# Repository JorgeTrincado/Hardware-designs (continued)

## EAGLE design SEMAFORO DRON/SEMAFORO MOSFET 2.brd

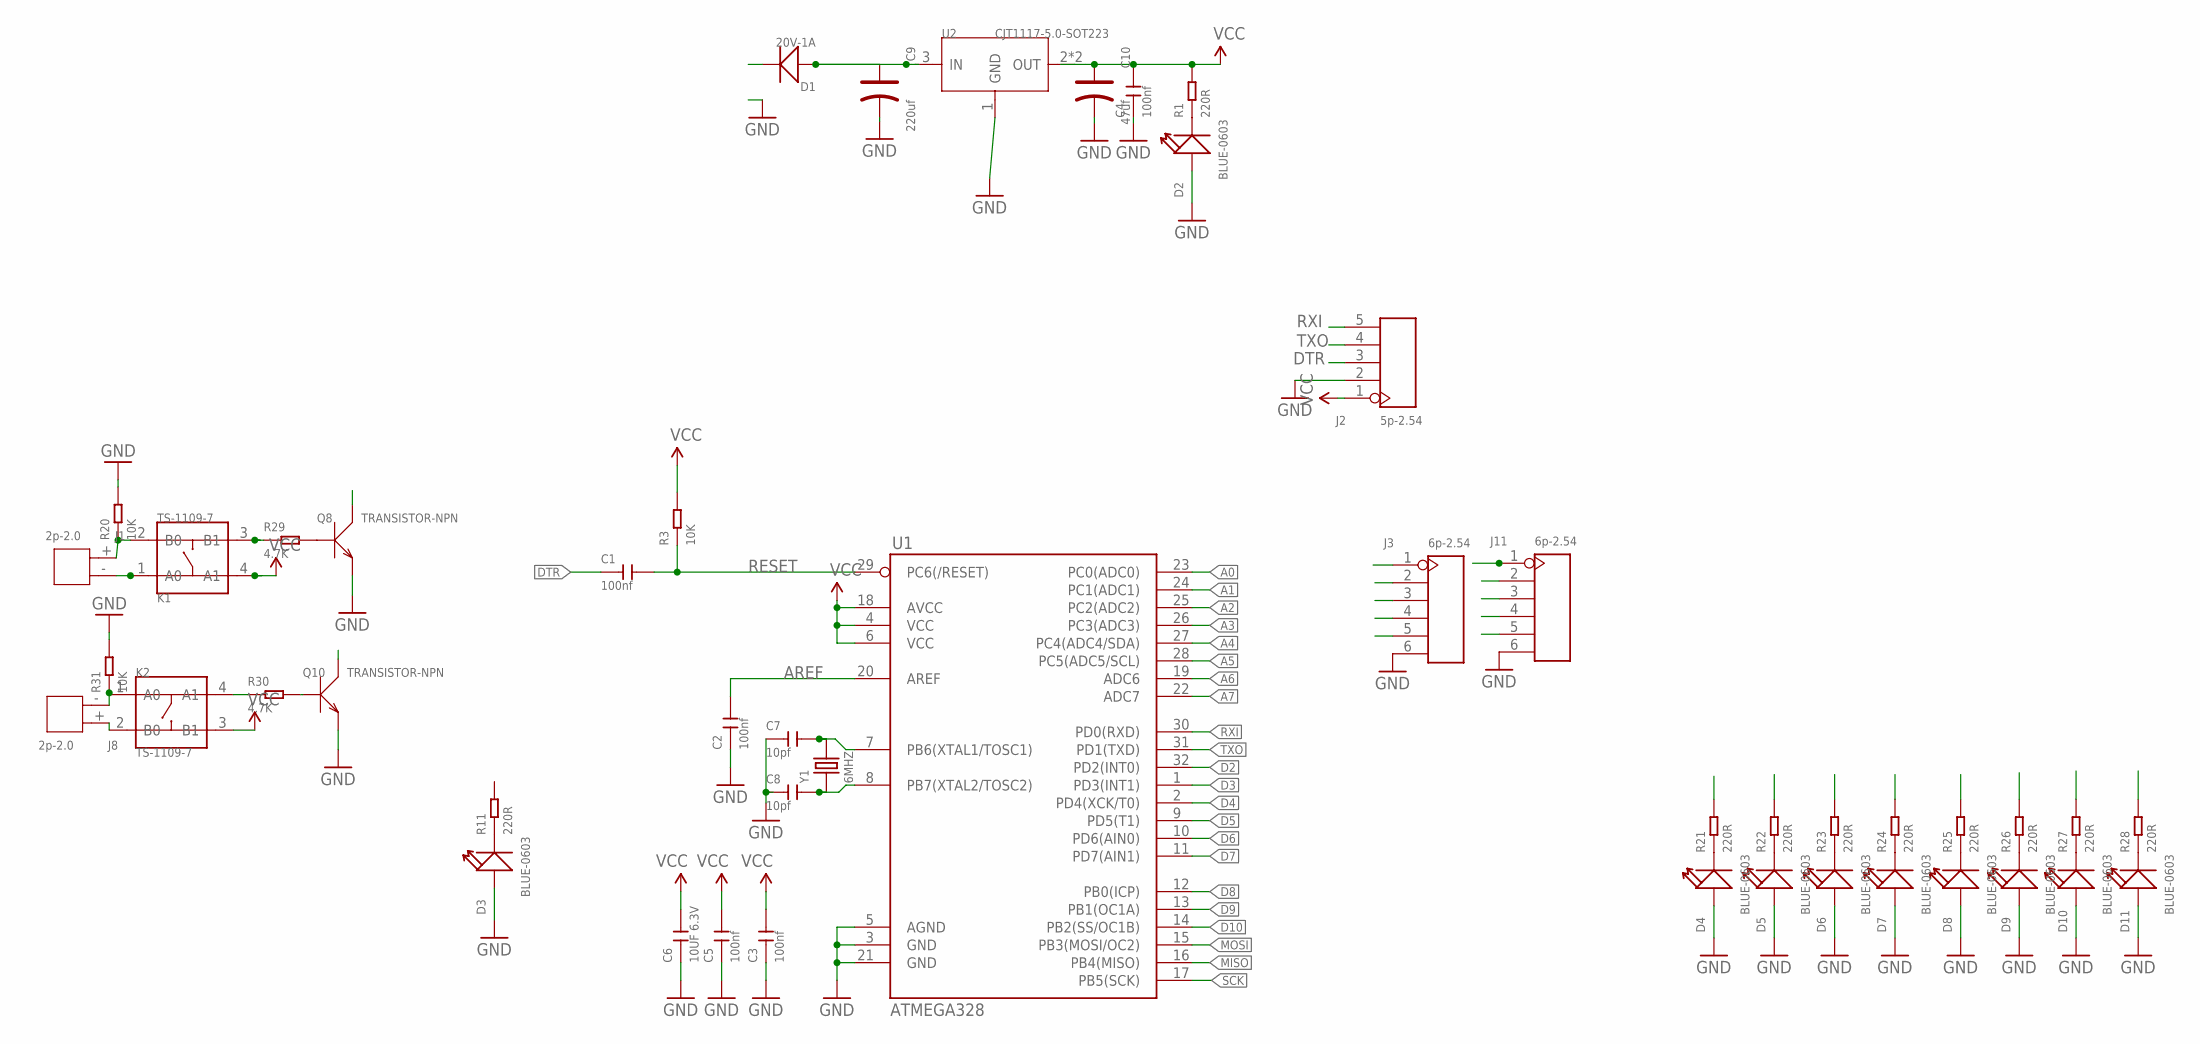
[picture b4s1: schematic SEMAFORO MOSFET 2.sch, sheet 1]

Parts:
C1, C2, C3, C4, C5: 100nf; C0603
C6: 10UF 6.3V; C0603
C7, C8: 10pf; C0603
C9: 220uf; PC-D5.3MM
C10: 47uf; PC-D5.3MM
D1: 20V-1A; SOD-123
D2, D3, D4, D5, D6, D7, D8, D9, D10, D11: BLUE-0603; LED-0603
J1, J8: 2p-2.0; H2-2.0-6X4.5MM
J2: 5p-2.54; H5-2.54
J3, J11: 6p-2.54; H6-2.54
K1, K2: TS-1109-7; SW4-6.2X6.2X5.0MM
Q8, Q10: TRANSISTOR-NPN; SOT-23
R1, R11, R21, R22, R23, R24, R25, R26, R27, R28: 220R; R0603
R3, R20, R31: 10K; R0603
R29, R30: 4.7K; R0603
U1: ATMEGA328; TQFP32-08
U2: CJT1117-5.0-SOT223; SOT-223
Y1: 6MHZ; HC49US

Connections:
3.3V: K1.4 (A1), K2.3 (B1)
A0: J11.3, U1.23 (PC0(ADC0))
A1: J11.2, U1.24 (PC1(ADC1))
A2: J3.5, U1.25 (PC2(ADC2))
A3: J3.4, U1.26 (PC3(ADC3))
A4: J3.3, U1.27 (PC4(ADC4/SDA))
A5: J3.2, U1.28 (PC5(ADC5/SCL))
A6: J11.5, U1.19 (ADC6)
A7: J11.4, U1.22 (ADC7)
AREF: C2.2, U1.20 (AREF)
D2: Q8.3 (C), U1.32 (PD2(INT0))
D3: U1.1 (PD3(INT1))
D4: U1.2 (PD4(XCK/T0))
D5: R21.2, U1.9 (PD5(T1)); also elsewhere on the board
D6: R22.2, U1.10 (PD6(AIN0)); also elsewhere on the board
D7: R23.2, U1.11 (PD7(AIN1)); also elsewhere on the board
D8: R24.2, U1.12 (PB0(ICP)); also elsewhere on the board
D9: R25.2, U1.13 (PB1(OC1A)); also elsewhere on the board
D10: R28.2, U1.14 (PB2(SS/OC1B)); also elsewhere on the board
D22: J1.+, K1.2 (B0), R20.1
DTR: C1.1, J2.3
GND: C2.1, C3.1, C4.1, C5.1, C6.1, C7.1, C8.1, C9.-, C10.-, D2.+, D3.+, D4.+, D5.+, D6.+, D7.+, D8.+, D9.+, D10.+, D11.+, J2.2, J3.6, J11.6, Q8.2 (E), Q10.2 (E), R20.2, R31.2, U1.3 (GND), U1.5 (AGND), U1.21 (GND), U2.1 (GND); also elsewhere on the board
MISO: R26.2, U1.16 (PB4(MISO)); also elsewhere on the board
MOSI: R27.2, U1.15 (PB3(MOSI/OC2)); also elsewhere on the board
unnamed: C8.2, U1.8 (PB7(XTAL2/TOSC2)), Y1.1
unnamed: C7.2, U1.7 (PB6(XTAL1/TOSC1)), Y1.2
unnamed: D2.-, R1.1
unnamed: D4.-, R21.1
unnamed: C9.+, D1.+, U2.3 (IN)
unnamed: D3.-, R11.1
unnamed: J8.-, K2.1 (A0), R31.1
unnamed: J8.+, K2.2 (B0)
unnamed: D5.-, R22.1
unnamed: D6.-, R23.1
unnamed: D7.-, R24.1
unnamed: D8.-, R25.1
unnamed: D9.-, R26.1
unnamed: D10.-, R27.1
unnamed: D11.-, R28.1
unnamed: K2.4 (A1), R30.1
unnamed: K1.3 (B1), R29.1
unnamed: Q10.1 (B), R30.2
unnamed: Q8.1 (B), R29.2
RESET: C1.2, Q10.3 (C), R3.1, U1.29 (PC6(/RESET))
RXI: J2.5, U1.30 (PD0(RXD))
SCK: U1.17 (PB5(SCK))
TXO: J2.4, U1.31 (PD1(TXD))
VCC: C3.2, C4.2, C5.2, C6.2, C10.+, J1.-, J2.1, J3.1, J11.1, K1.1 (A0), R1.2, R3.2, U1.4 (VCC), U1.6 (VCC), U1.18 (AVCC), U2.2 (OUT), U2.TER (OUT)

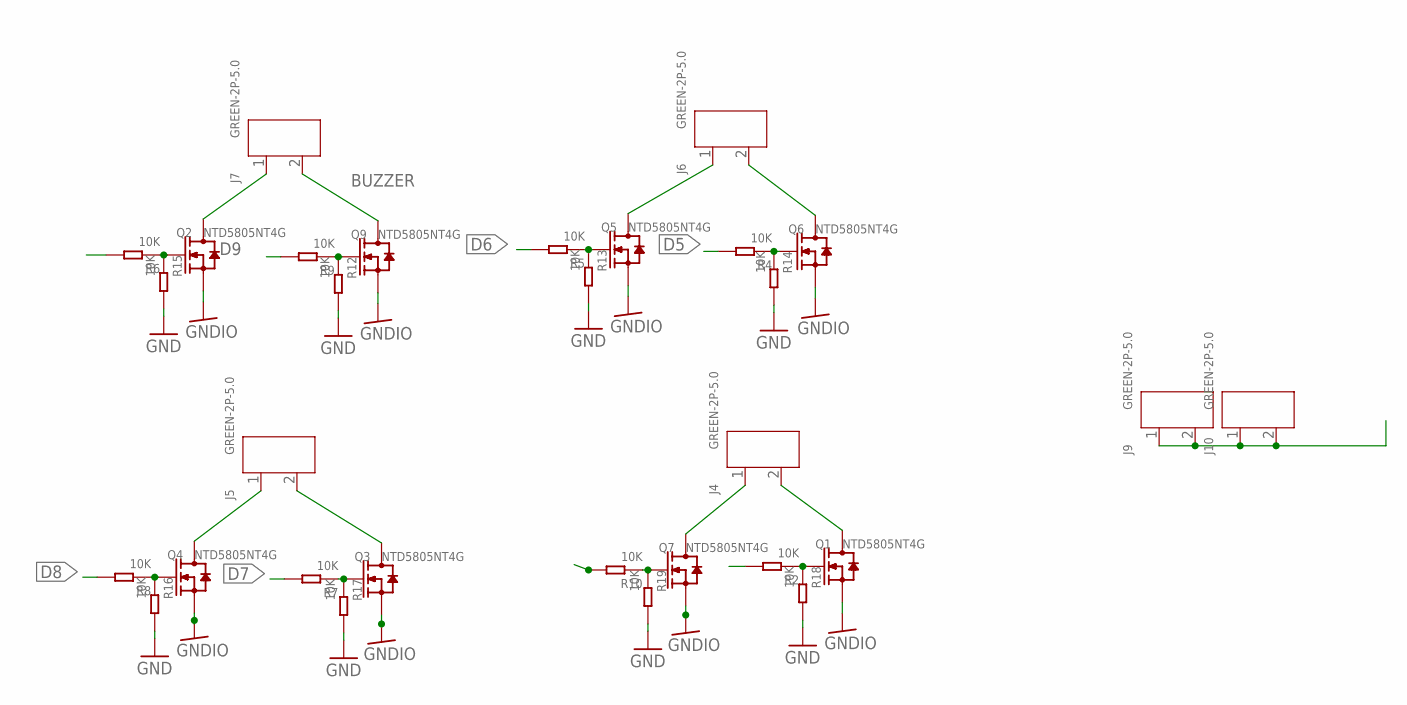
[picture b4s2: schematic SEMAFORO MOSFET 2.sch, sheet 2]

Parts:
J4, J5, J6, J7, J9, J10: GREEN-2P-5.0; H2-5.0-10.5X8.0MM
Q1, Q2, Q3, Q4, Q5, Q6, Q7, Q9: NTD5805NT4G; DPAK
R2, R4, R5, R6, R7, R8, R9, R10, R12, R13, R14, R15, R16, R17, R18, R19: 10K; R0603

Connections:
BUZZER: J7.2, Q9.3 (D)
D5: R4.2; also elsewhere on the board
D6: R5.2; also elsewhere on the board
D7: R7.2; also elsewhere on the board
D8: R8.2; also elsewhere on the board
D9: R9.2; also elsewhere on the board
D10: R6.2; also elsewhere on the board
GND: R12.2, R13.2, R14.2, R15.2, R16.2, R17.2, R18.2, R19.2; also elsewhere on the board
GNDIO: Q1.2 (S), Q2.2 (S), Q3.2 (S), Q4.2 (S), Q5.2 (S), Q6.2 (S), Q7.2 (S), Q9.2 (S)
MISO: R10.2; also elsewhere on the board
MOSI: R2.2; also elsewhere on the board
unnamed: J9.1, J9.2, J10.1, J10.2
unnamed: J4.1, Q7.3 (D)
unnamed: Q1.1 (G), R2.1, R18.1
unnamed: Q6.1 (G), R4.1, R14.1
unnamed: Q9.1 (G), R9.1, R12.1
unnamed: Q7.1 (G), R10.1, R19.1
unnamed: Q5.1 (G), R5.1, R13.1
unnamed: Q2.1 (G), R6.1, R15.1
unnamed: Q3.1 (G), R7.1, R17.1
unnamed: Q4.1 (G), R8.1, R16.1
R1: J5.1, Q4.3 (D)
R2: J5.2, Q3.3 (D)
R3: J6.1, Q5.3 (D)
V1: J6.2, Q6.3 (D)
V2: J4.2, Q1.3 (D)
V3: J7.1, Q2.3 (D)

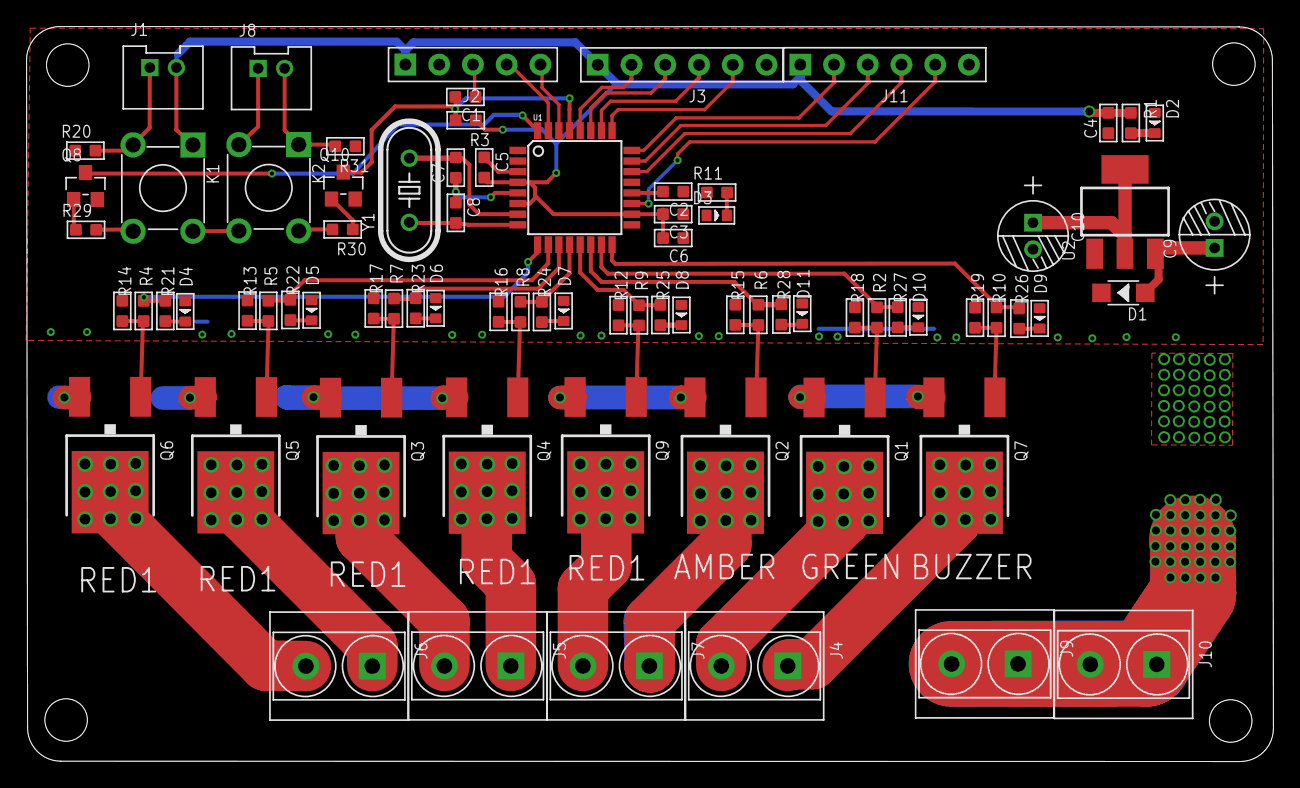
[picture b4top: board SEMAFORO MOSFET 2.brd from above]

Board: 2 copper layers, 93.9 x 55.3 mm, 78 parts (0 on the bottom side), 63 nets.

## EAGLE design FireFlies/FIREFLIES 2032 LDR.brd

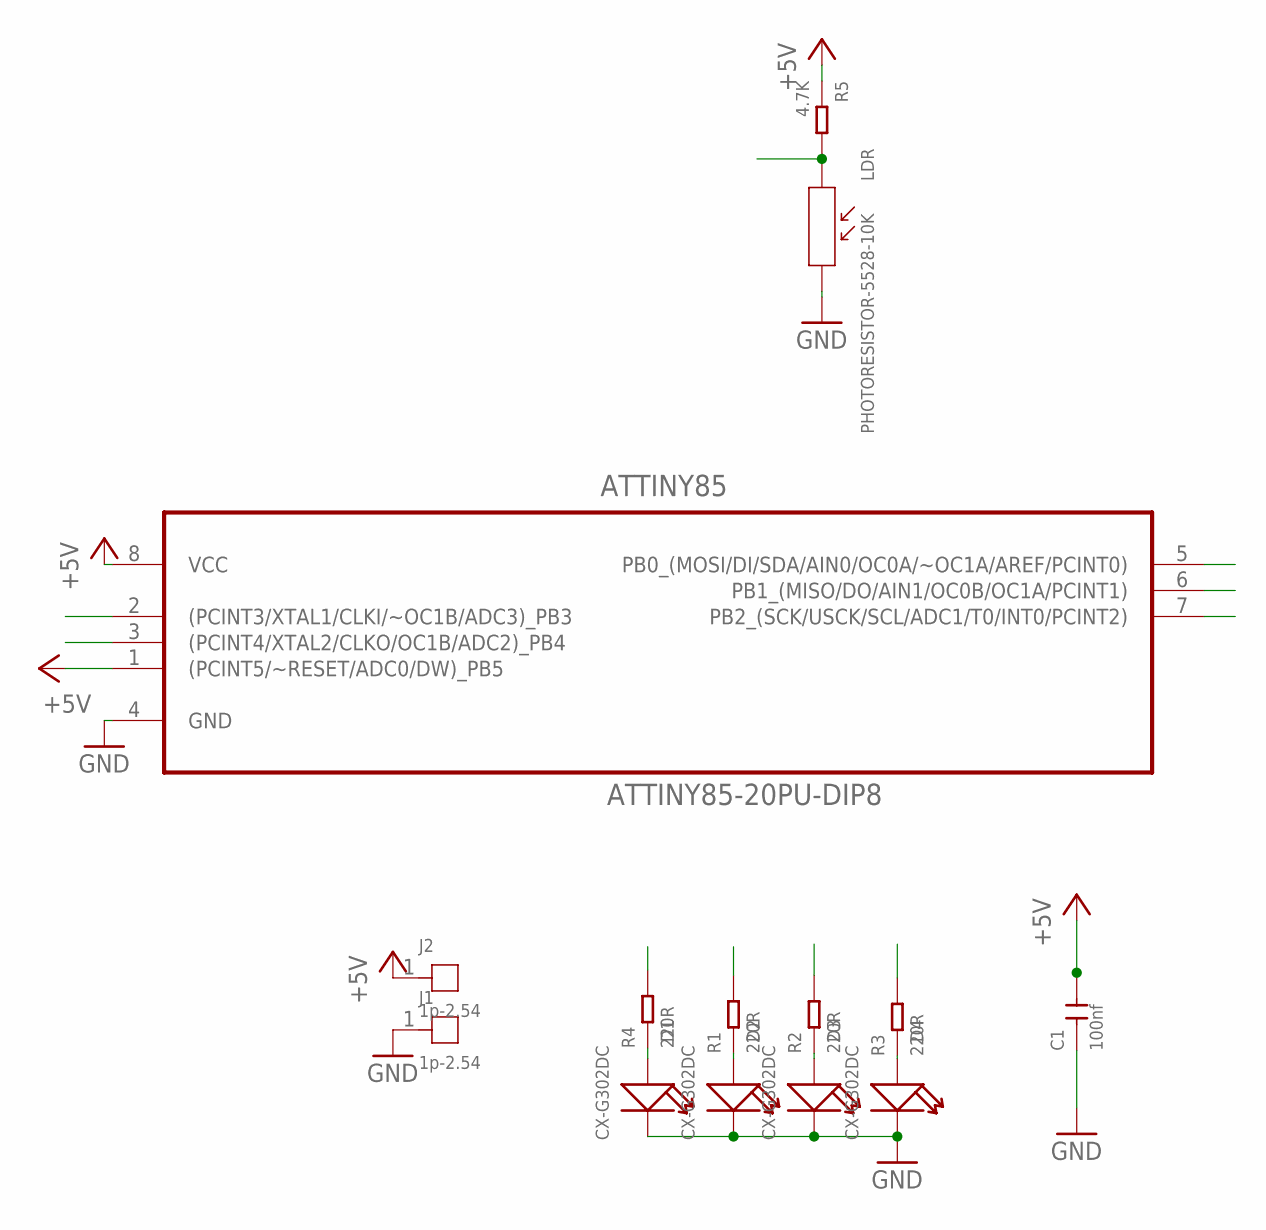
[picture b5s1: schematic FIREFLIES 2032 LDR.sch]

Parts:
ATTINY85: ATTINY85-20PU-DIP8; DIP254P762X533-8
C1: 100nf; CERAMIC-2.54
D1, D2, D3, D4: CX-G302DC; LED2-2.54-D3.0MM
J1, J2: 1p-2.54; 1P-65/35MIL
LDR: PHOTORESISTOR-5528-10K; SNR2-3.0
R1, R2, R3, R4: 220R; PR-D2.3XL6.5MM
R5: 4.7K; PR-D2.3XL6.5MM

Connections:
+5V: ATTINY85.1 ((PCINT5/~RESET/ADC0/DW)_PB5), ATTINY85.8 (VCC), C1.2, J2.1, R5.1
A1: ATTINY85.7 (PB2_(SCK/USCK/SCL/ADC1/T0/INT0/PCINT2)), LDR.1, R5.2
A2: ATTINY85.3 ((PCINT4/XTAL2/CLKO/OC1B/ADC2)_PB4), R2.2
A3: ATTINY85.2 ((PCINT3/XTAL1/CLKI/~OC1B/ADC3)_PB3), R1.2
D0: ATTINY85.5 (PB0_(MOSI/DI/SDA/AIN0/OC0A/~OC1A/AREF/P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), R3.2
D1: ATTINY85.6 (PB1_(MISO/DO/AIN1/OC0B/OC1A/PCINT1)), R4.2
GND: ATTINY85.4 (GND), C1.1, D1.K (-), D2.K (-), D3.K (-), D4.K (-), J1.1, LDR.2
unnamed: D2.A (+), R1.1
unnamed: D1.A (+), R4.1
unnamed: D3.A (+), R2.1
unnamed: D4.A (+), R3.1

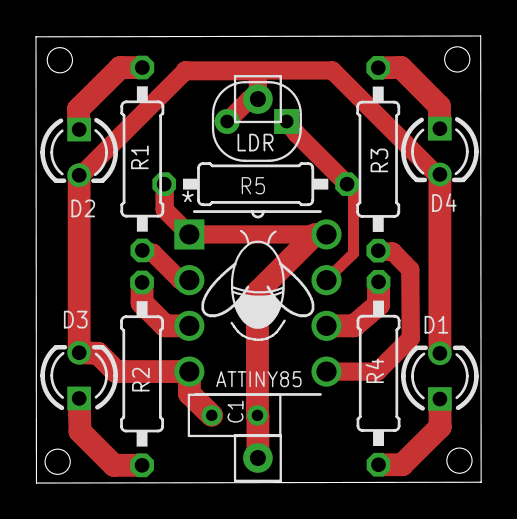
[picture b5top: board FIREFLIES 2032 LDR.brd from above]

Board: 2 copper layers, 24.7 x 24.8 mm, 14 parts (0 on the bottom side), 11 nets.
